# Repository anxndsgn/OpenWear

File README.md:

# OpenWear
## A Toolkit for Rapid Textile Circuit Prototyping

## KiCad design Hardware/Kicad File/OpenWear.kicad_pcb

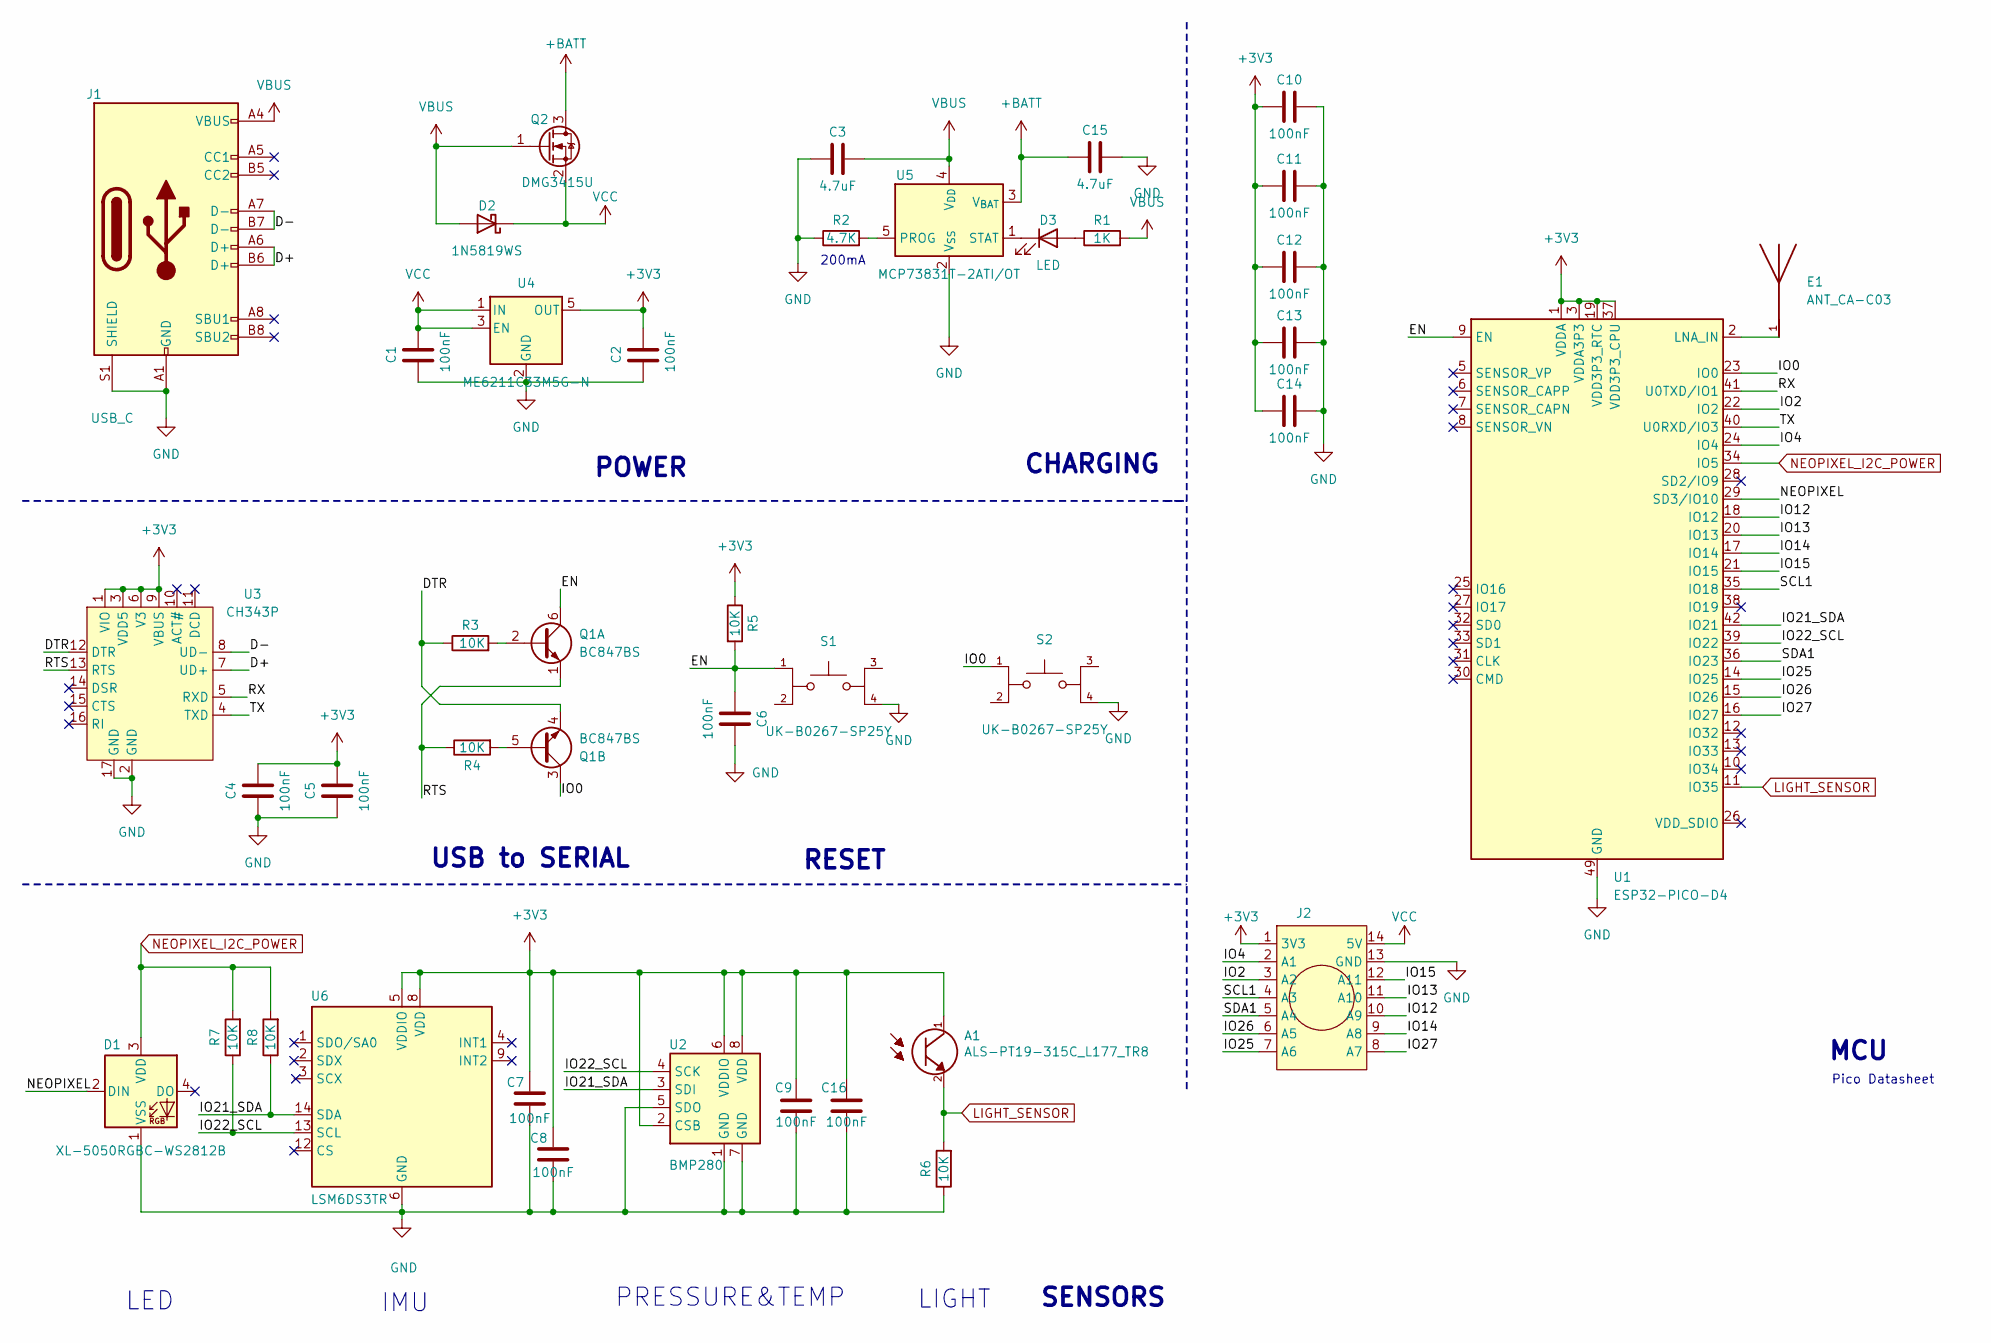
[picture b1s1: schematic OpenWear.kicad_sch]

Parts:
A1: ALS-PT19-315C_L177_TR8; XDCR_ALS-PT19-315C_L177_TR8; LCSC Part # C146233
C1, C2, C4, C5, C6, C7, C8, C9, C10, C11, C12, C13, C14, C16: 100nF; C_0603_1608Metric
C3, C15: 4.7uF; C_0603_1608Metric
D1: XL-5050RGBC-WS2812B; LED_Inolux_IN-PI554FCH_PLCC4_5.0x5.0mm_P3.2mm; LCSC Part # C2843785
D2: 1N5819WS; D_SOD-323; LCSC Part # C191023
D3: LED; LED_0603_1608Metric
E1: ANT_CA-C03; XCVR_YC0010AA; LCSC Part # C9900003739
J1: USB_C; USB_C_Receptacle_G-Switch_GT-USB-7010ASV; LCSC Part # C9900016956
J2: Connector; RING
Q1: BC847BS; SOT-363_SC-70-6; LCSC Part # C8653
Q2: DMG3415U; SOT-23; LCSC Part # C7202986
R1: 1K; R_0603_1608Metric
R2: 4.7K; R_0603_1608Metric
R3, R4, R5, R6, R7, R8: 10K; R_0603_1608Metric
S1: UK-B0267-SP25Y; SW_TL3365AF180QG; LCSC Part # C493283
S2: UK-B0267-SP25Y; SW_TL3365AF180QG
U1: ESP32-PICO-D4; QFN-48-1EP_7x7mm_P0.5mm_EP5.3x5.3mm; LCSC Part # C2832759
U2: BMP280; Bosch_LGA-8_2x2.5mm_P0.65mm_ClockwisePinNumbering; LCSC Part # C83291
U3: CH343P; QFN-16-1EP_3x3mm_P0.5mm_EP1.9x1.9mm; LCSC Part # C2846043
U4: ME6211C33M5G-N; SOT-23-5; LCSC Part # C82942
U5: MCP73831T-2ATI/OT; SOT-23-5; LCSC Part # C14879
U6: LSM6DS3TR; LGA-14_3x2.5mm_P0.5mm_LayoutBorder3x4y; LCSC Part # C95230

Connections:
+3V3: A1.1, C2.1, C4.1, C5.1, C7.1, C8.1, C9.1, C10.2, C11.2, C12.2, C13.2, C14.2, C16.1, J2.1 (3V3), R5.1, U1.1 (VDDA), U1.3 (VDDA3P3), U1.4 (VDDA3P3), U1.19 (VDD3P3_RTC), U1.37 (VDD3P3_CPU), U1.43 (VDDA), U1.46 (VDDA), U2.2 (CSB), U2.6 (VDDIO), U2.8 (VDD), U3.1 (VIO), U3.3 (VDD5), U3.6 (V3), U3.9 (VBUS), U4.5 (OUT), U6.5 (VDDIO), U6.8 (VDD)
+BATT: C15.2, Q2.3 (D), U5.3 (V_{BAT})
/D+: J1.A6 (D+), J1.B6 (D+), U3.7 (UD+)
/D-: J1.A7 (D-), J1.B7 (D-), U3.8 (UD-)
/DTR: Q1.4 (E2), R3.1, U3.12 (DTR)
/EN: C6.2, Q1.6 (C1), R5.2, S1.1, U1.9 (EN)
/IO0: Q1.3 (C2), S2.1, U1.23 (IO0)
/IO2: J2.3 (A2), U1.22 (IO2)
/IO4: J2.2 (A1), U1.24 (IO4)
/IO12: J2.10 (A9), U1.18 (IO12)
/IO13: J2.11 (A10), U1.20 (IO13)
/IO14: J2.9 (A8), U1.17 (IO14)
/IO15: J2.12 (A11), U1.21 (IO15)
/IO21_SDA: R8.1, U1.42 (IO21), U2.3 (SDI), U6.14 (SDA)
/IO22_SCL: R7.1, U1.39 (IO22), U2.4 (SCK), U6.13 (SCL)
/IO25: J2.7 (A6), U1.14 (IO25)
/IO26: J2.6 (A5), U1.15 (IO26)
/IO27: J2.8 (A7), U1.16 (IO27)
/NEOPIXEL: D1.2 (DIN), U1.29 (SD3/IO10)
/RTS: Q1.1 (E1), R4.1, U3.13 (RTS)
/RX: U1.41 (U0TXD/IO1), U3.5 (RXD)
/SCL1: J2.4 (A3), U1.35 (IO18)
/SDA1: J2.5 (A4), U1.36 (IO23)
/TX: U1.40 (U0RXD/IO3), U3.4 (TXD)
GND: C1.2, C2.2, C3.2, C4.2, C5.2, C6.1, C7.2, C8.2, C9.2, C10.1, C11.1, C12.1, C13.1, C14.1, C15.1, C16.2, D1.1 (VSS), J1.A1 (GND), J1.A12 (GND), J1.B1 (GND), J1.B12 (GND), J1.S1 (SHIELD), J2.13 (GND), R2.1, R6.1, S1.4, S2.4, U1.49 (GND), U2.1 (GND), U2.5 (SDO), U2.7 (GND), U3.2 (GND), U3.17 (GND), U4.2 (GND), U5.2 (V_{SS}), U6.6 (GND), U6.7 (GND)
LIGHT_SENSOR: A1.2, R6.2, U1.11 (IO35)
NEOPIXEL_I2C_POWER: D1.3 (VDD), R7.2, R8.2, U1.34 (IO5)
unnamed: D3.2 (A), R1.1
unnamed: D3.1 (K), U5.1 (STAT)
unnamed: Q1.2 (B1), R3.2
unnamed: Q1.5 (B2), R4.2
unnamed: E1.1, U1.2 (LNA_IN)
unnamed: R2.2, U5.5 (PROG)
VBUS: C3.1, D2.2 (A), J1.A4 (VBUS), J1.A9 (VBUS), J1.B4 (VBUS), J1.B9 (VBUS), Q2.1 (G), R1.2, U5.4 (V_{DD})
VCC: C1.1, D2.1 (K), J2.14 (5V), Q2.2 (S), U4.1 (IN), U4.3 (EN)

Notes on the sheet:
Pico Datasheet
CHARGING
LIGHT
MCU
200mA
RESET
SENSORS
IMU
POWER
USB to SERIAL
LED
PRESSURE&TEMP

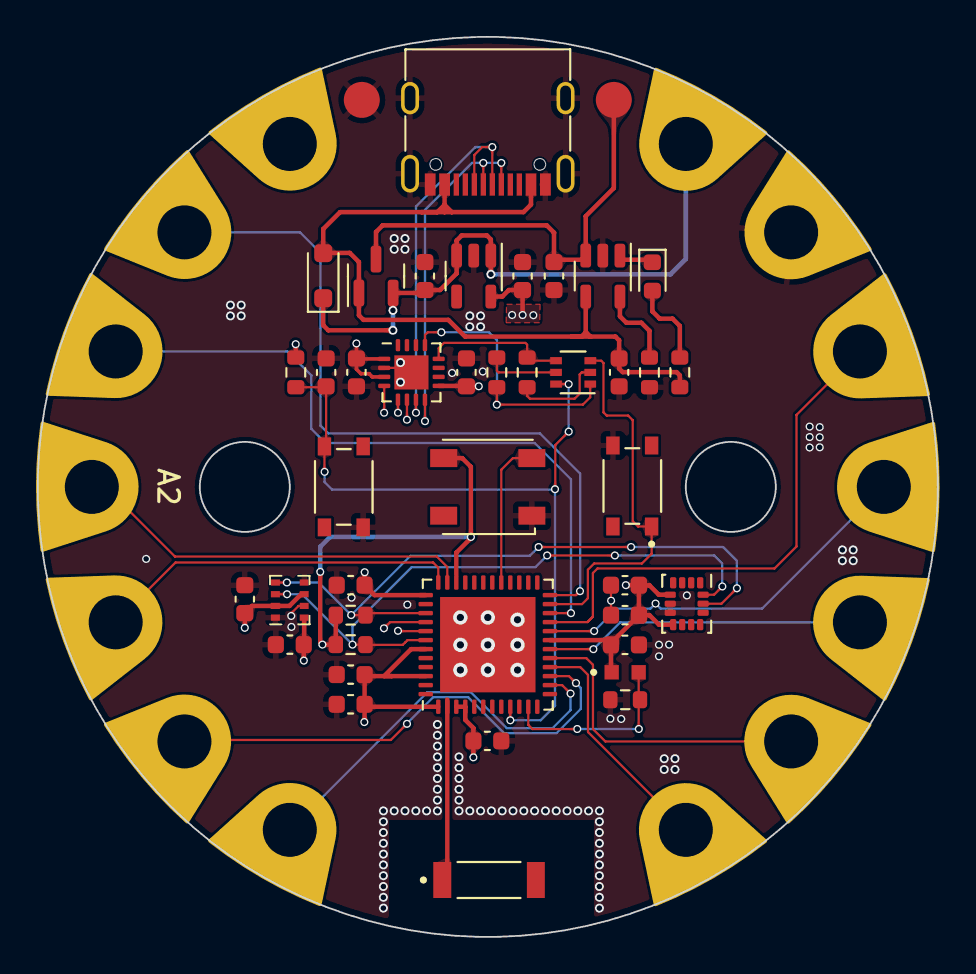
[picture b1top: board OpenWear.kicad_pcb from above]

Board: 4 copper layers, 50.0 x 50.0 mm, 41 parts (0 on the bottom side), 35 nets.

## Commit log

2023-10-05 add gerber.zip
2023-10-16 add arduino code
2023-10-16 add kicad file
2023-10-17 update code
2023-10-17 update sch
2023-10-17 update kicad
2023-10-17 update pcb
2023-10-17 test
2023-10-17 add license
2023-10-17 Rename License.txt to License
2023-10-18 add backup
2023-10-18 add example code
2023-11-01 update PCB layout
2023-11-02 update pcb and sch
2023-11-08 update gerber
2023-12-08 UPDATEV0.3
2023-12-12 add mircopython code
2023-12-12 update examplecode

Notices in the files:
Hardware/Kicad File/OpenWear.kicad_pcb:
CC-BY-SA
Hardware/Kicad File/OpenWear.kicad_sch:
CC-BY-SA 3.0
